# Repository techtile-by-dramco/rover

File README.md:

## Documentation

- The `rpi` folder contains the Python scripts to collect the sensor readings from the sensor-reader (`Sensorcombiner.py`) and driving the motors (with the rotary encoderers).
- The `scissor-lift` folder contains the files to talk the the scissor lift microcontrollers (Adruino Uno + custom-made shield) through Python. More information is included in the [docs](https://jarnevanmulders.github.io/scissor-lift-docs/).
- The `sensor-reader`folder contains the source files for the microcontroller to read-out all sensors on the rover. This microcontroller is read-out by the RPI on the rover (as dicussed above).

## System Architecture

## System Description
To speed-up measurements, reduce labor-intensive tasks and mitigate human-errors, we have designed a rover
to perform automated 3D sampling inside the testbed. The rover consists of a baseplate, hosting the processing
unit and batteries, and a scissor lift to move the measurement equipment to the required height.

### Baseplate 
The baseplate contains a Raspberry Pi. A 16 cells battery pack, in a 4S4P configuration, powers the system. 
The battery voltage ranges from 10 V to 16.2 V depending on the charge state. The battery back, based on Lithium Cobalt Oxide (LCO) technology,
has a capacity of 170Wh and can handle up to 480W peak power. Besides powering the rover, the battery pack
provides power to the peripherals and measurement equipment in order to conduct the experiments. When
the battery is low, the rover is able to navigate to its charging station, recharge and resume the measurements.

### Navigation
Marvelmind indoor RTLS is used as a positioning system. It has a precision of 2 cm.
Ultrasonic beacons are used to acquire the position of the mobile beacon (mounted on the baseplate). Four
beacons are fixed in the Techtile infrastructure. The position is determined by trilateration. To filter out
outliers, we make use of a Kalman filter. The recursive algorithm uses consecutive inputs to estimate the
current state. Based on the uncertainties of the inputs and the uncertainties of the previous estimates, the
current state is approximated. Besides localization, the rover features obstacle detection to mitigate crashing into objects in the room. 
Ultrasonic sensors mounted on the sides of the rover’s baseplate are used and have
a resolution of 3 mm and a range of 2 cm to 400 cm.

### Scissor lift.
The baseplate of the rover can navigate through the room in 2D space. By mounting the scissor
lift on top of the baseplate, the rover is able to measure in 3D space. The lift has a range of 55 cm
to 185 cm. The equipment can be mounted on top of the lift. Power is supplied to the equipment from the
battery pack. The scissor lift can be controlled with AT-commands. The height of the lift is determined by
the VL53L1X Time-of-Flight (ToF) sensor using a 940 nm invisible Class 1 laser. An advertised accuracy and
ranging error of ± 20 mm in both ambient light and dark light conditions.

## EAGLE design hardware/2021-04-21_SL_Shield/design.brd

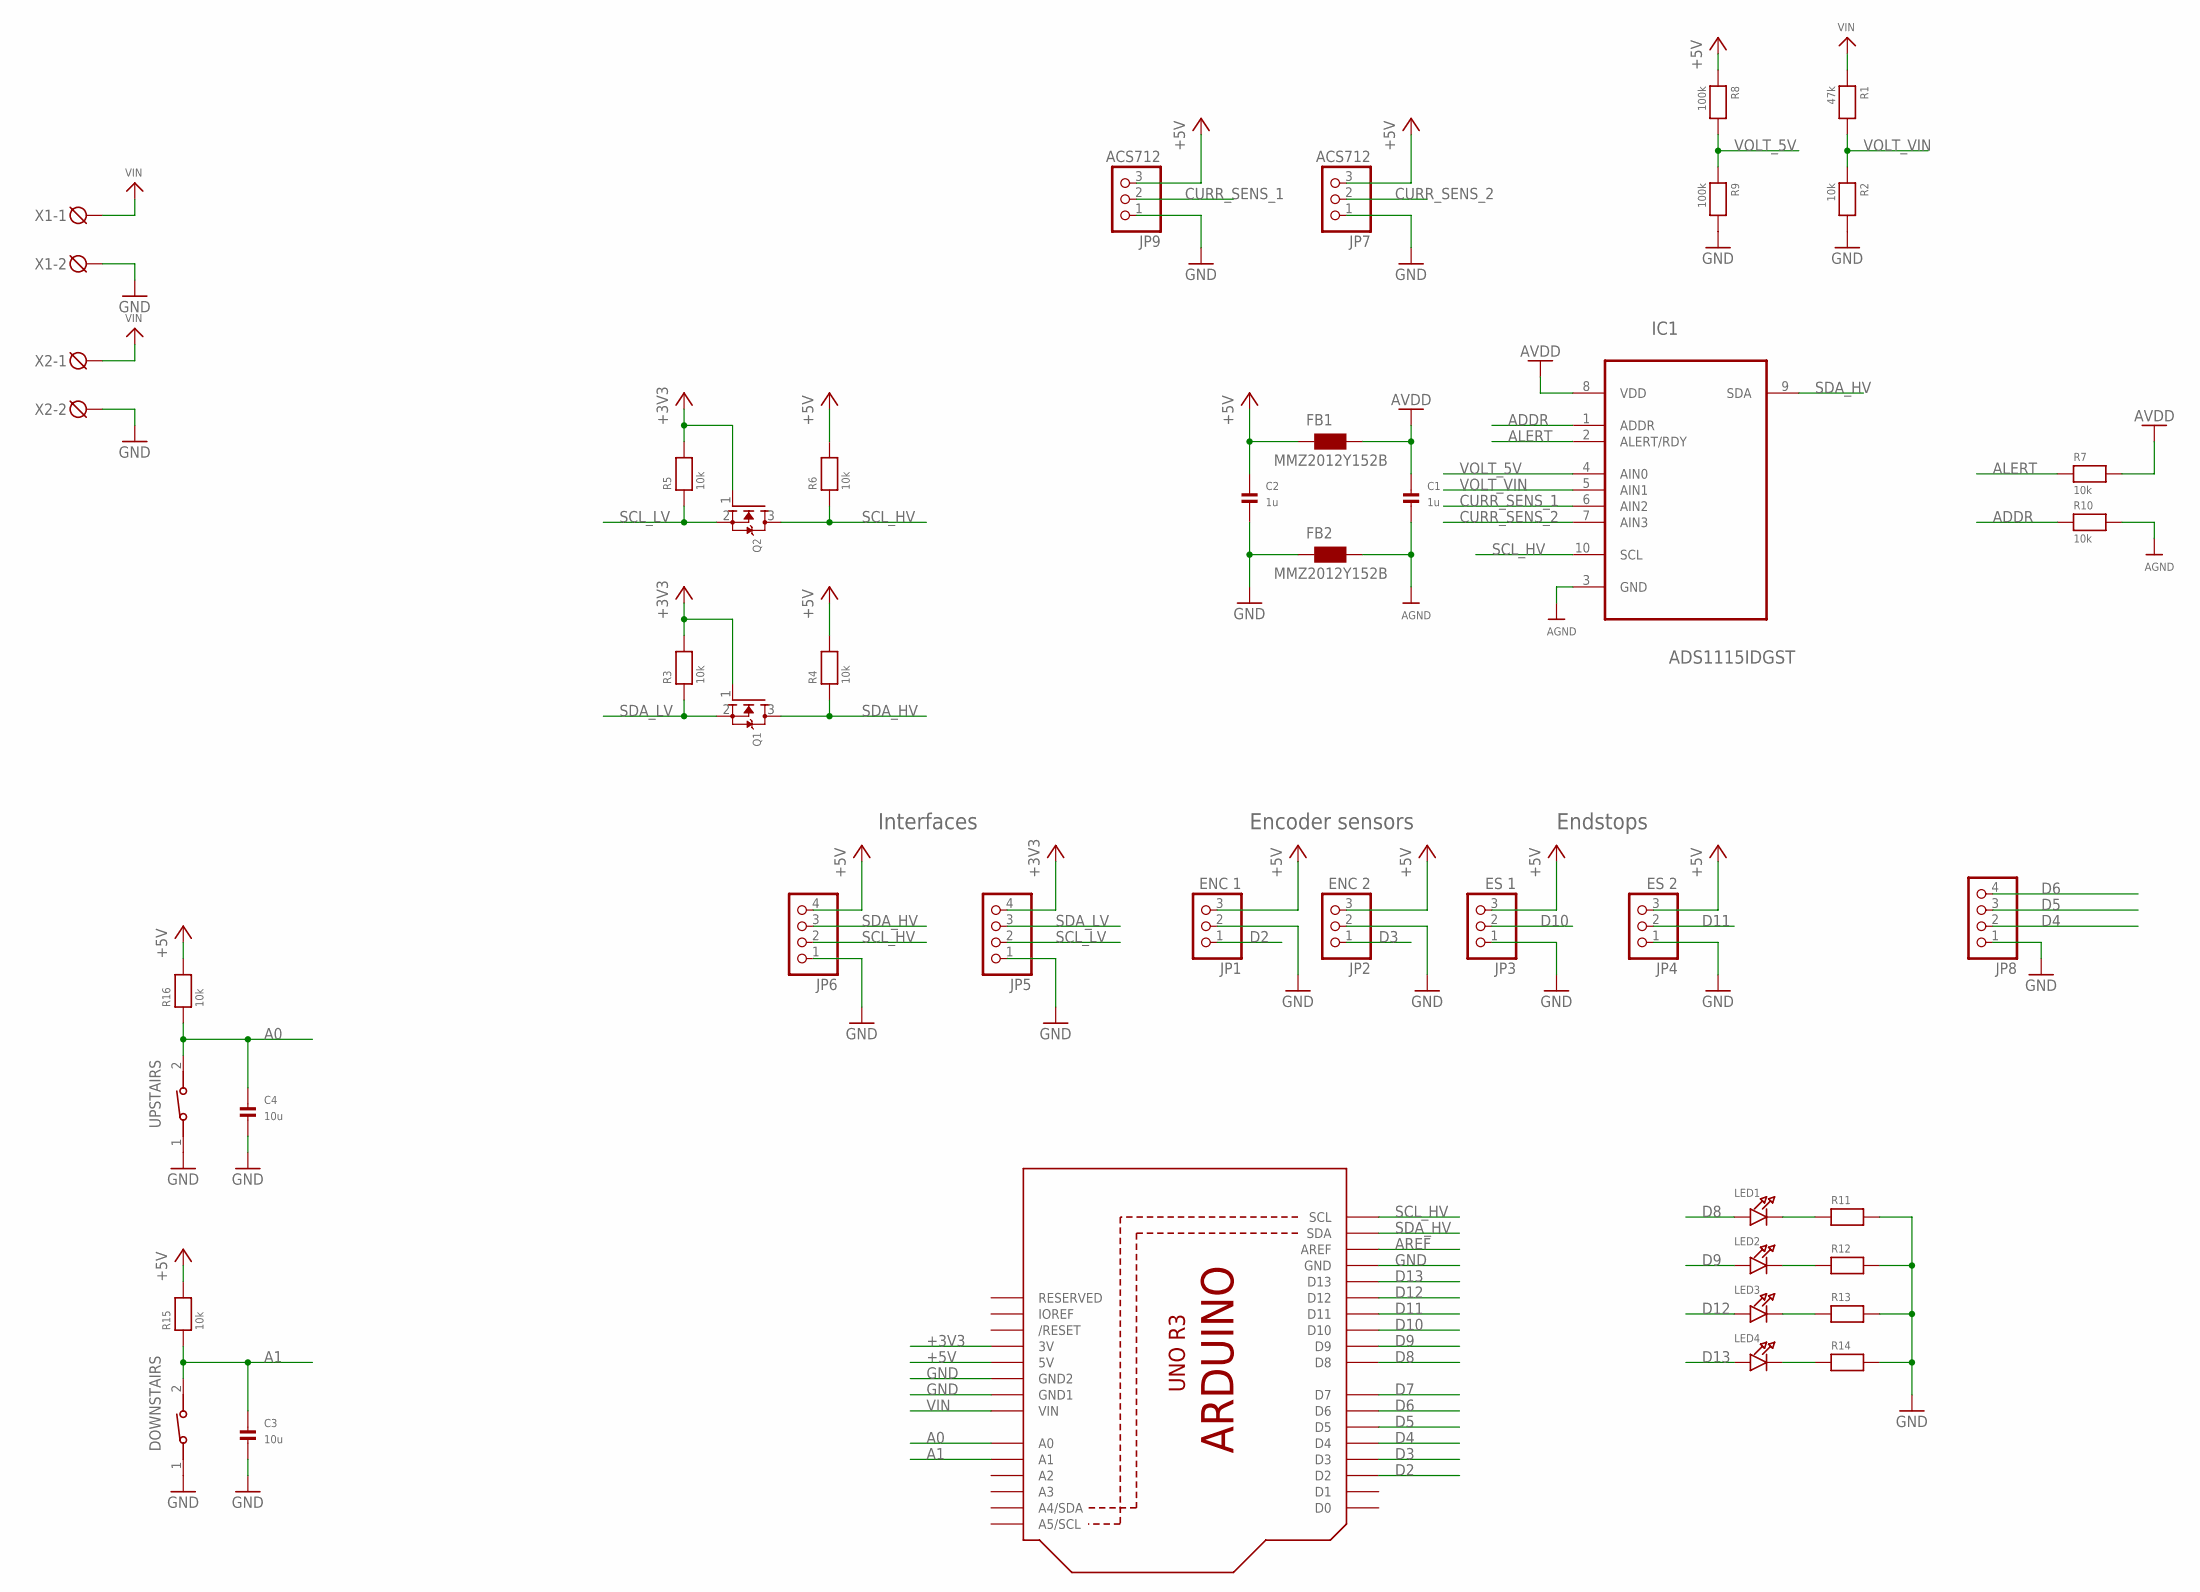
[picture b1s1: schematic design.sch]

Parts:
C1, C2: 1u; 0805
C3, C4: 10u; 0805
DOWNSTAIRS: 434111043826
FB1, FB2: MMZ2012Y152B; 0805
IC1: ADS1115IDGST; SOP50P490X110-10N
JP1: ENC 1; 1X03_ROUND
JP2: ENC 2; 1X03_ROUND
JP3: ES 1; 1X03_ROUND
JP4: ES 2; 1X03_ROUND
JP5, JP6, JP8: HEADER-1X4ROUND; 1X04_ROUND
JP7, JP9: ACS712; 1X03_ROUND
LED1, LED2, LED3, LED4: LED0805; CHIPLED_0805
Q1, Q2: MOSFET-NWIDE; SOT23-WIDE
R1: 47k; 0603
R2, R3, R4, R5, R6, R7, R10, R15, R16: 10k; 0603
R8, R9: 100k; 0603
R11, R12, R13, R14: RESISTOR0603; 0603
U1: ARDUINOR3NODIM; ARDUINOR3-NODIM
UPSTAIRS: 434111043826
X1, X2: DG3XX-02-5.0; DG306-5.0-02P

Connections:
+3V3: JP5.4, Q1.1 (G), Q2.1 (G), R3.2, R5.2, U1.3V
+5V: C2.1, FB1.1, JP1.3, JP2.3, JP3.3, JP4.3, JP6.4, JP7.3, JP9.3, R4.2, R6.2, R8.1, R15.2, R16.2, U1.5V
A0: C4.1, R16.1, U1.A0, UPSTAIRS.2
A1: C3.1, DOWNSTAIRS.2, R15.1, U1.A1
ADDR: IC1.1 (ADDR), R10.1
AGND: C1.2, FB2.2, IC1.3 (GND), R10.2
ALERT: IC1.2 (ALERT/RDY), R7.1
AREF: U1.AREF
AVDD: C1.1, FB1.2, IC1.8 (VDD), R7.2
CURR_SENS_1: IC1.6 (AIN2), JP9.2
CURR_SENS_2: IC1.7 (AIN3), JP7.2
D2: JP1.1, U1.D2
D3: JP2.1, U1.D3
D4: JP8.2, U1.D4
D5: JP8.3, U1.D5
D6: JP8.4, U1.D6
D7: U1.D7
D8: LED1.A, U1.D8
D9: LED2.A, U1.D9
D10: JP3.2, U1.D10
D11: JP4.2, U1.D11
D12: LED3.A, U1.D12
D13: LED4.A, U1.D13
GND: C2.2, C3.2, C4.2, DOWNSTAIRS.1, FB2.1, JP1.2, JP2.2, JP3.1, JP4.1, JP5.1, JP6.1, JP7.1, JP8.1, JP9.1, R2.2, R9.2, R11.2, R12.2, R13.2, R14.2, U1.GND, U1.GND1, U1.GND2, UPSTAIRS.1, X1.2, X2.2
unnamed: LED1.C, R11.1
unnamed: LED2.C, R12.1
unnamed: LED3.C, R13.1
unnamed: LED4.C, R14.1
SCL_HV: IC1.10 (SCL), JP6.2, Q2.3 (D), R6.1, U1.SCL
SCL_LV: JP5.2, Q2.2 (S), R5.1
SDA_HV: IC1.9 (SDA), JP6.3, Q1.3 (D), R4.1, U1.SDA
SDA_LV: JP5.3, Q1.2 (S), R3.1
VIN: R1.1, U1.VIN, X1.1, X2.1
VOLT_5V: IC1.4 (AIN0), R8.2, R9.1
VOLT_VIN: IC1.5 (AIN1), R1.2, R2.1

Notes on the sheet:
Encoder sensors
Endstops
Interfaces

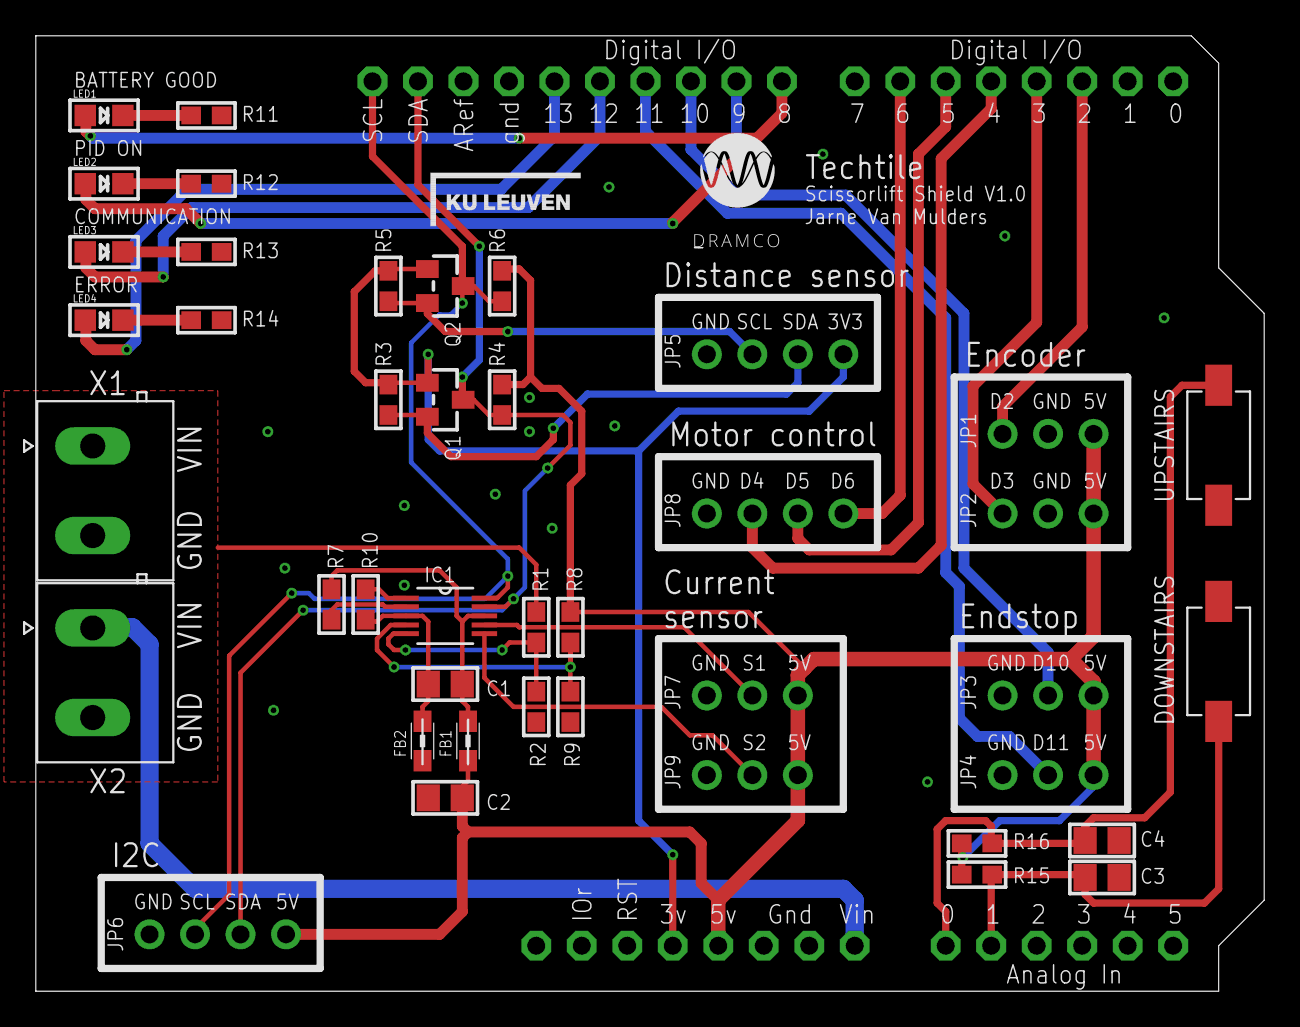
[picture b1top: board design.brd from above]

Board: 2 copper layers, 68.6 x 53.3 mm, 43 parts (0 on the bottom side), 33 nets.

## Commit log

2023-02-15 update clean-up
2023-03-20 Add encoder motor files

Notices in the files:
parts and their libraries:
microbuilder: This work is placed in the public domain, and may be freely used for commercial and non-commercial work with the following conditions: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
wuerth-elektronik: Copyright: Würth Elektronik eiSos
Eagle_SWITCHES: Copyright: Würth Elektronik
supply0: Copyright (C) 2007, Bob Starr
